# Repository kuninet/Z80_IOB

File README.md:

View this project on [CADLAB.io](https://cadlab.io/project/23712). 

# Z80 I/Oボード (KZ80-IOB)

詳細は[以下のwiki](https://github.com/kuninet/Z80_IOB/wiki)にまとめます。
ご覧ください。

https://github.com/kuninet/Z80_IOB/wiki

## 概要

- SBC8080ルーズキットバスにつながるI/Oボードです。
  - [Z80 CPUボード(KZ80-CPUB)](https://github.com/kuninet/Z80_CPUB/wiki)、[SBC8080](https://vintagechips.wordpress.com/2018/06/24/sbc8080-cpu%E3%83%AB%E3%83%BC%E3%82%BA%E3%82%AD%E3%83%83%E3%83%88/)、[SBC8085](https://vintagechips.wordpress.com/2018/08/27/sbc8085%e3%81%8c%e5%ae%8c%e6%88%90/)と組み合わせた稼働を確認しています。
  - 8255パラレルI/O LSIを搭載しています。(Lチカに最適)
  - 8251シリアルチップを搭載しています。
  - 将来 ArduinoコネクタのFM音源シールドを搭載するためのコネクタを装備しています。(これ以外の使いみちはありませんが...)

## 回路図

[回路図はこちら](image/Z80-8251-PPI.pdf)です。

## 部品表

[部品表はこちら](KiCAD/Z80-8251-PPI.ods)です。

※LibreOffice/OpenOfficeのcalcで開ける形式となっています。

## ライセンス

- 本リポジトリのデータは MIT License のもとで公開します。[LICENSE.txt](LICENSE.txt)を参照して下さい。

## その他注意点等

- 8251シリアルLSIのアドレスデコードをSBC8080 SUBボードと合わせる場合は、アドレスデコードジャンパ(J2)の1-2を短絡(I/Oアドレス:00h)してください。
- 8255パラレルI/O LSIのアドレスデコードジャンパ(J3)は 13-14を短絡(I/Oアドレス:C0h)が推奨です。

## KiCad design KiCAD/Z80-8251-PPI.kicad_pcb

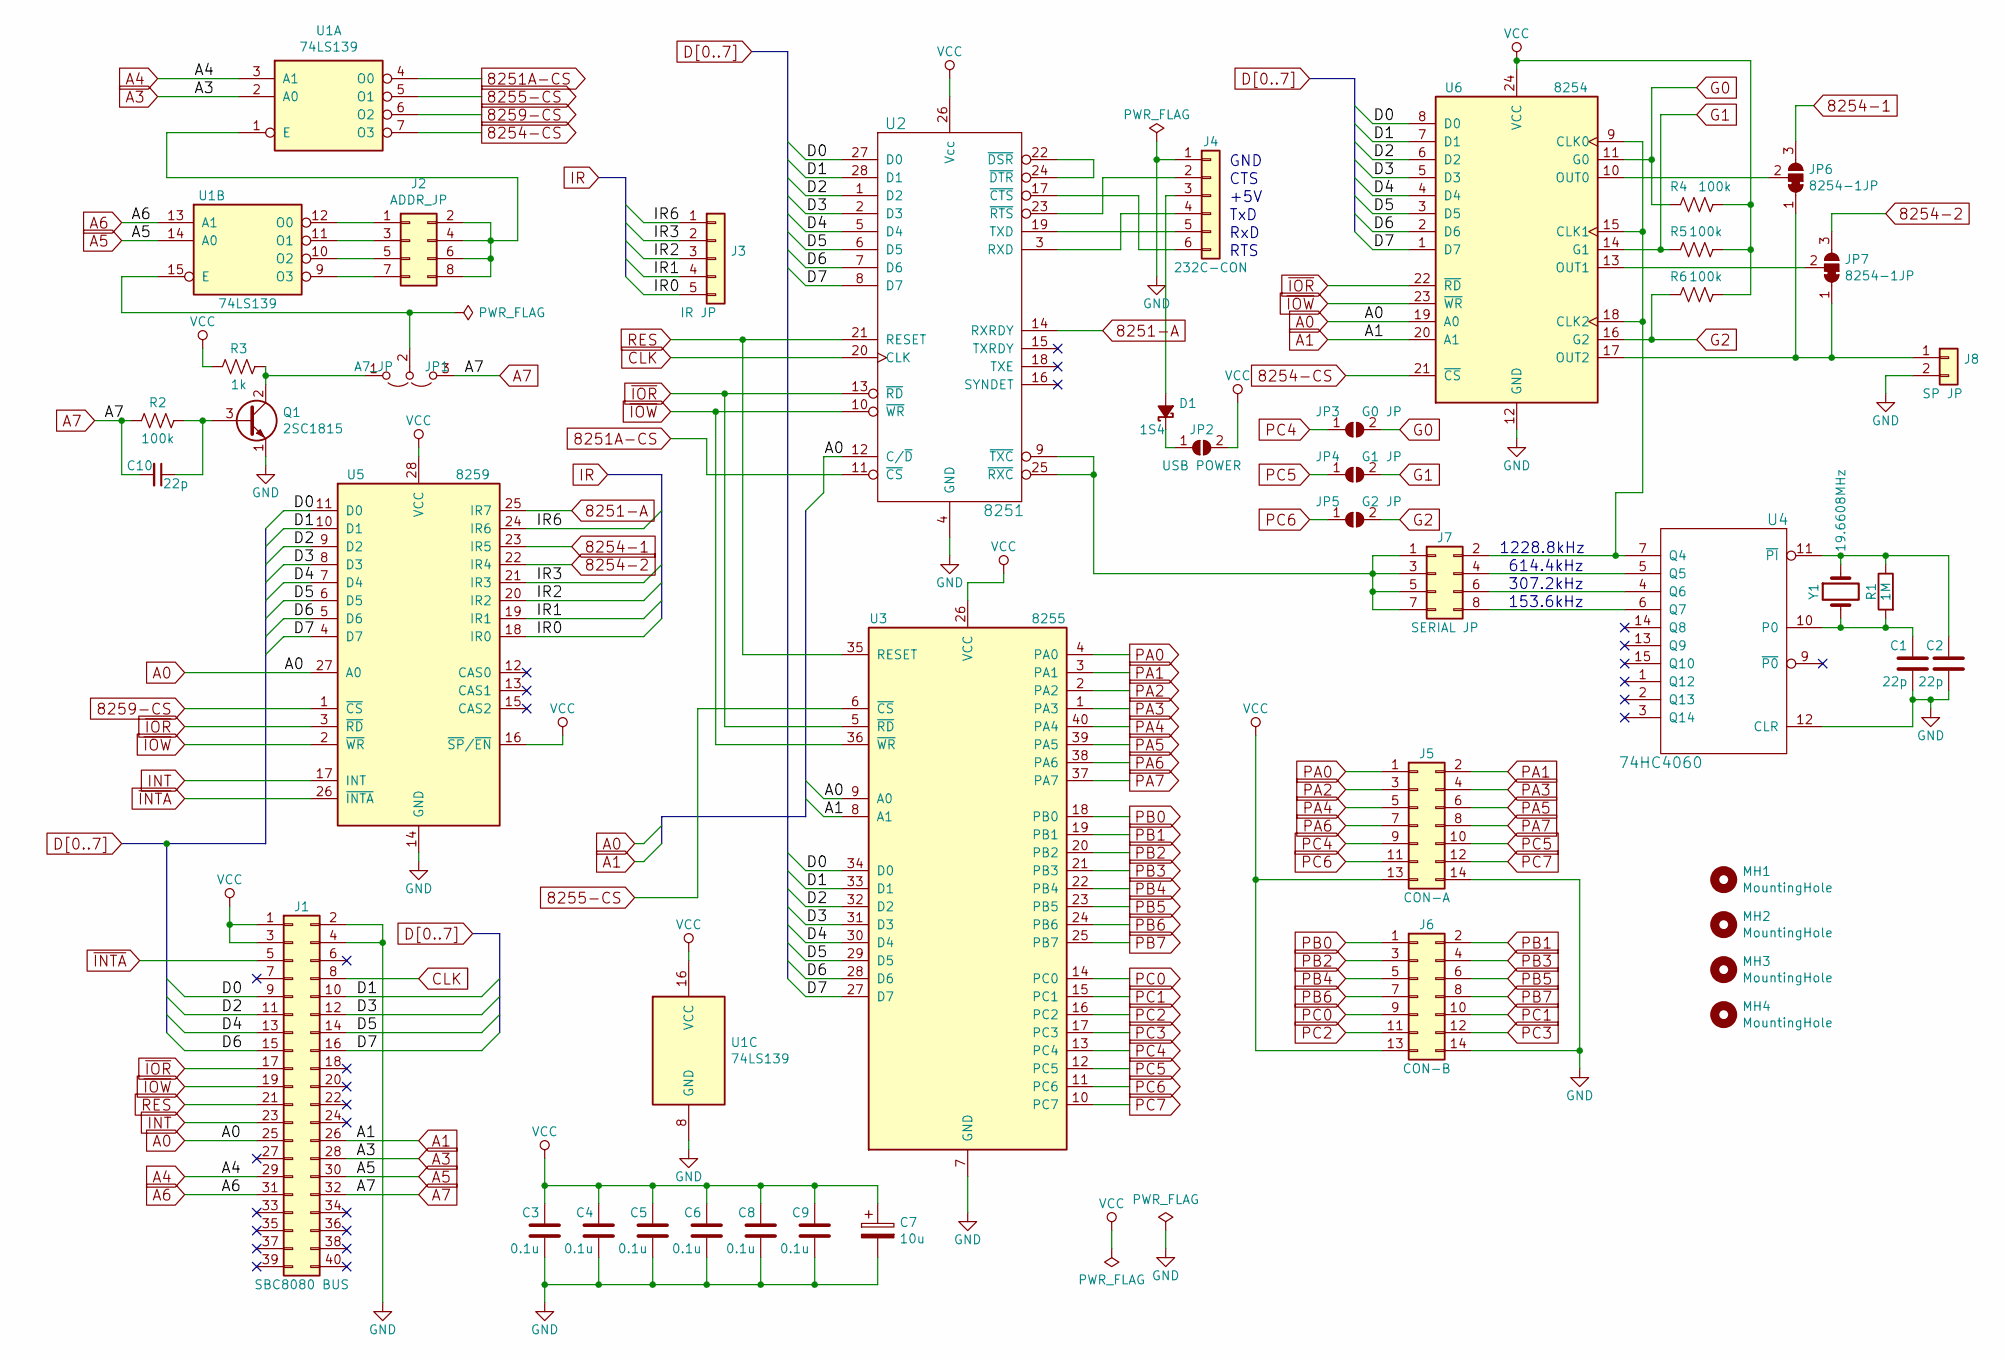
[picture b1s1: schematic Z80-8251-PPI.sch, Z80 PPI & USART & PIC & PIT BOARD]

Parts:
C1, C2, C10: 22p; C_Disc_D3.0mm_W1.6mm_P2.50mm
C3, C4, C5, C6, C8, C9: 0.1u; C_Disc_D3.0mm_W1.6mm_P2.50mm
C7: 10u; CP_Radial_D5.0mm_P2.50mm
D1: 1S4; D_DO-34_SOD68_P7.62mm_Horizontal
J1: SBC8080 BUS; Pin_Header_Angled_2x20
J2: ADDR_JP; PinHeader_2x04_P2.54mm_Vertical
J3: IR JP; PinHeader_1x05_P2.54mm_Horizontal
J4: 232C-CON; PinHeader_1x06_P2.54mm_Horizontal
J5: CON-A; PinHeader_2x07_P2.54mm_Vertical
J6: CON-B; PinHeader_2x07_P2.54mm_Vertical
J7: SERIAL JP; PinHeader_2x04_P2.54mm_Vertical
J8: SP JP; PinHeader_1x02_P2.54mm_Horizontal
JP1: A7_JP; PinHeader_1x03_P2.54mm_Vertical
JP2: USB POWER; SolderJumper-2_P1.3mm_Open_RoundedPad1.0x1.5mm
JP3: G0 JP; SolderJumper-2_P1.3mm_Open_RoundedPad1.0x1.5mm
JP4: G1 JP; SolderJumper-2_P1.3mm_Open_RoundedPad1.0x1.5mm
JP5: G2 JP; SolderJumper-2_P1.3mm_Open_RoundedPad1.0x1.5mm
JP6, JP7: 8254-1JP; SolderJumper-3_P1.3mm_Bridged12_RoundedPad1.0x1.5mm
MH1, MH2, MH3, MH4: MountingHole; MountingHole_3.2mm_M3
Q1: 2SC1815; TO-92_Inline_Wide
R1: 1M; R_Axial_DIN0207_L6.3mm_D2.5mm_P10.16mm_Horizontal
R2, R4, R5, R6: 100k; R_Axial_DIN0207_L6.3mm_D2.5mm_P10.16mm_Horizontal
R3: 1k; R_Axial_DIN0207_L6.3mm_D2.5mm_P10.16mm_Horizontal
U1: 74LS139; DIP-16_W7.62mm_Socket
U2: 8251; DIP-28_W15.24mm_Socket
U3: 8255; DIP-40_W15.24mm_Socket
U4: 74HC4060; DIP-16_W7.62mm_Socket
U5: 8259; DIP-28_W15.24mm_Socket
U6: 8254; DIP-24_W15.24mm_Socket
Y1: 19.6608MHz; HC-49V

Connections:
8251-A: U2.14 (RXRDY), U5.25 (IR7)
8251A-CS: U1.4 (O0), U2.11 (~CS)
8254-1: JP6.3 (B), U5.23 (IR5)
8254-2: JP7.3 (B), U5.22 (IR4)
8254-CS: U1.7 (O3), U6.21 (~CS~)
8255-CS: U1.5 (O1), U3.6 (~CS~)
8259-CS: U1.6 (O2), U5.1 (~CS~)
/IR0: J3.5, U5.18 (IR0)
/IR1: J3.4, U5.19 (IR1)
/IR2: J3.3, U5.20 (IR2)
/IR3: J3.2, U5.21 (IR3)
/IR6: J3.1, U5.24 (IR6)
A0: J1.25, U2.12 (C/~D), U3.9 (A0), U5.27 (A0), U6.19 (A0)
A1: J1.26, U3.8 (A1), U6.20 (A1)
A3: J1.28, U1.2 (A0)
A4: J1.29, U1.3 (A1)
A5: J1.30, U1.14 (A0)
A6: J1.31, U1.13 (A1)
A7: C10.2, J1.32, JP1.3 (B), R2.2
CLK: J1.8, U2.20 (CLK)
D0: J1.9, U2.27 (D0), U3.34 (D0), U5.11 (D0), U6.8 (D0)
D1: J1.10, U2.28 (D1), U3.33 (D1), U5.10 (D1), U6.7 (D1)
D2: J1.11, U2.1 (D2), U3.32 (D2), U5.9 (D2), U6.6 (D2)
D3: J1.12, U2.2 (D3), U3.31 (D3), U5.8 (D3), U6.5 (D3)
D4: J1.13, U2.5 (D4), U3.30 (D4), U5.7 (D4), U6.4 (D4)
D5: J1.14, U2.6 (D5), U3.29 (D5), U5.6 (D5), U6.3 (D5)
D6: J1.15, U2.7 (D6), U3.28 (D6), U5.5 (D6), U6.2 (D6)
D7: J1.16, U2.8 (D7), U3.27 (D7), U5.4 (D7), U6.1 (D7)
G0: JP3.2 (B), R4.2, U6.11 (G0)
G1: JP4.2 (B), R5.2, U6.14 (G1)
G2: JP5.2 (B), R6.2, U6.16 (G2)
GND: C1.2, C2.2, C3.2, C4.2, C5.2, C6.2, C7.2, C8.2, C9.2, J1.2, J1.4, J4.1, J5.14, J6.14, J8.2, Q1.1 (E), U1.8 (GND), U2.4 (GND), U3.7 (GND), U4.8 (GND), U4.12 (CLR), U5.14 (GND), U6.12 (GND)
INT: J1.23, U5.17 (INT)
unnamed: C1.1, R1.2, U4.10 (P0), Y1.2
unnamed: C2.1, R1.1, U4.11 (~PI), Y1.1
unnamed: C10.1, Q1.3 (B), R2.1
unnamed: D1.1 (K), JP2.1 (A)
unnamed: D1.2 (A), J4.3
unnamed: J2.1, U1.12 (O0)
unnamed: J2.2, J2.4, J2.6, J2.8, U1.1 (E)
unnamed: J2.3, U1.11 (O1)
unnamed: J2.5, U1.10 (O2)
unnamed: J2.7, U1.9 (O3)
unnamed: J4.2, U2.23 (~RTS)
unnamed: J4.4, U2.3 (RXD)
unnamed: J4.5, U2.19 (TXD)
unnamed: J4.6, U2.17 (~CTS)
unnamed: J7.1, J7.3, J7.5, J7.7, U2.9 (~TXC), U2.25 (~RXC)
unnamed: J7.2, U4.7 (Q4), U6.9 (CLK0), U6.15 (CLK1), U6.18 (CLK2)
unnamed: J7.4, U4.5 (Q5)
unnamed: J7.6, U4.4 (Q6)
unnamed: J7.8, U4.6 (Q7)
unnamed: J8.1, JP6.1 (A), JP7.1 (A), U6.17 (OUT2)
unnamed: JP1.1 (A), Q1.2 (C), R3.1
unnamed: JP1.2 (C), U1.15 (E)
unnamed: JP6.2 (C), U6.10 (OUT0)
unnamed: JP7.2 (C), U6.13 (OUT1)
unnamed: U2.22 (~DSR), U2.24 (~DTR)
PA0: J5.1, U3.4 (PA0)
PA1: J5.2, U3.3 (PA1)
PA2: J5.3, U3.2 (PA2)
PA3: J5.4, U3.1 (PA3)
PA4: J5.5, U3.40 (PA4)
PA5: J5.6, U3.39 (PA5)
PA6: J5.7, U3.38 (PA6)
PA7: J5.8, U3.37 (PA7)
PB0: J6.1, U3.18 (PB0)
PB1: J6.2, U3.19 (PB1)
PB2: J6.3, U3.20 (PB2)
PB3: J6.4, U3.21 (PB3)
PB4: J6.5, U3.22 (PB4)
PB5: J6.6, U3.23 (PB5)
PB6: J6.7, U3.24 (PB6)
PB7: J6.8, U3.25 (PB7)
PC0: J6.9, U3.14 (PC0)
PC1: J6.10, U3.15 (PC1)
PC2: J6.11, U3.16 (PC2)
PC3: J6.12, U3.17 (PC3)
PC4: J5.9, JP3.1 (A), U3.13 (PC4)
PC5: J5.10, JP4.1 (A), U3.12 (PC5)
PC6: J5.11, JP5.1 (A), U3.11 (PC6)
PC7: J5.12, U3.10 (PC7)
RES: J1.21, U2.21 (RESET), U3.35 (RESET)
VCC: C3.1, C4.1, C5.1, C6.1, C7.1, C8.1, C9.1, J1.1, J1.3, J5.13, J6.13, JP2.2 (B), R3.2, R4.1, R5.1, R6.1, U1.16 (VCC), U2.26 (Vcc), U3.26 (VCC), U4.16 (VCC), U5.16 (~SP~/~EN~), U5.28 (VCC), U6.24 (VCC)
~INTA: J1.5, U5.26 (~INTA~)
~IOR: J1.17, U2.13 (~RD), U3.5 (~RD~), U5.3 (~RD~), U6.22 (~RD~)
~IOW: J1.19, U2.10 (~WR), U3.36 (~WR~), U5.2 (~WR~), U6.23 (~WR~)

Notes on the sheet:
1228.8kHz
614.4kHz
307.2kHz
153.6kHz
GND
CTS
+5V
TxD
RxD
RTS

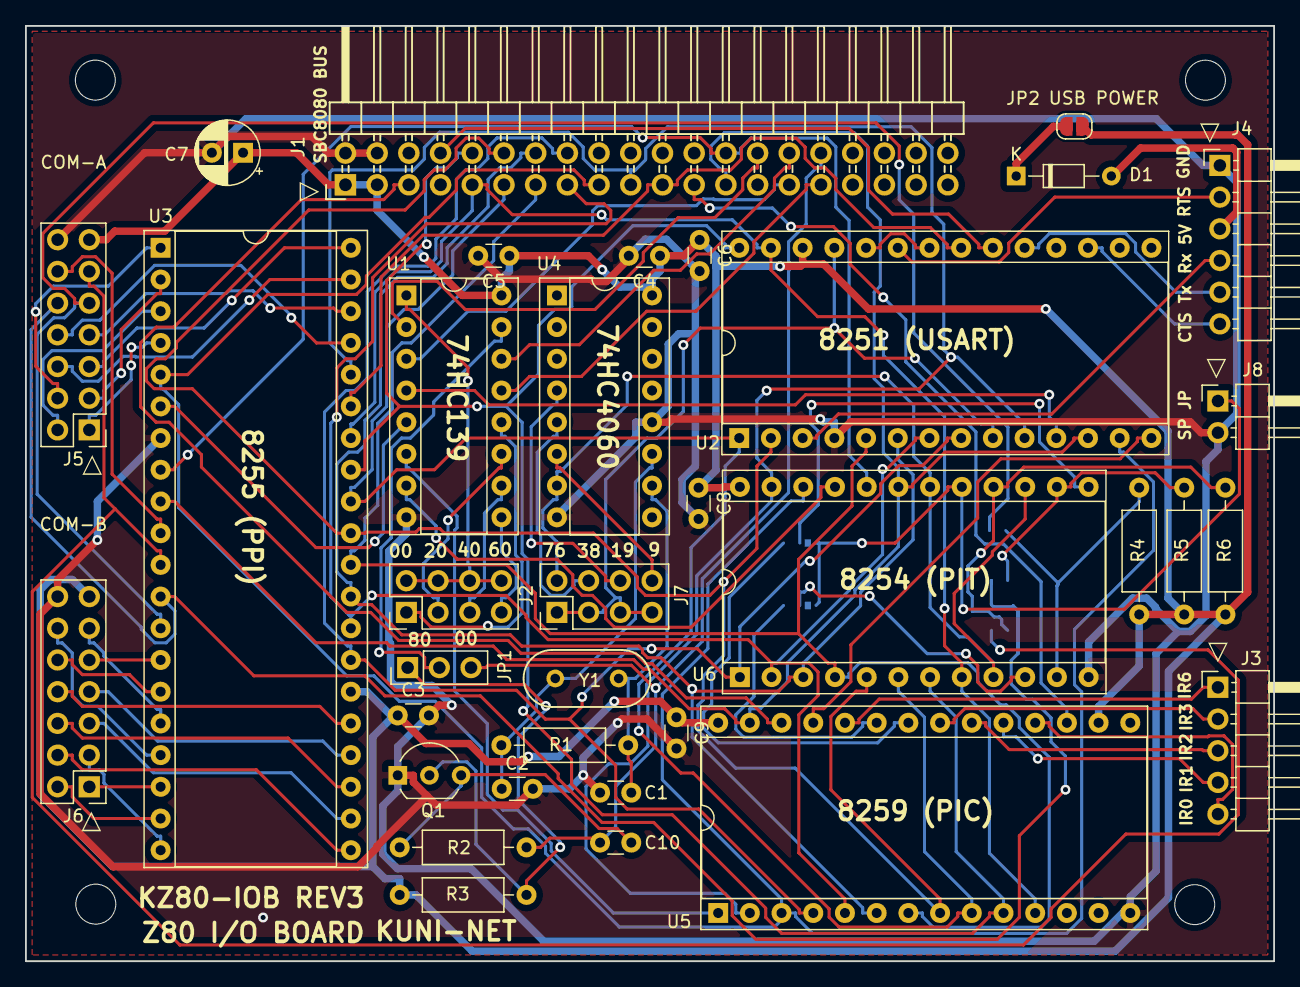
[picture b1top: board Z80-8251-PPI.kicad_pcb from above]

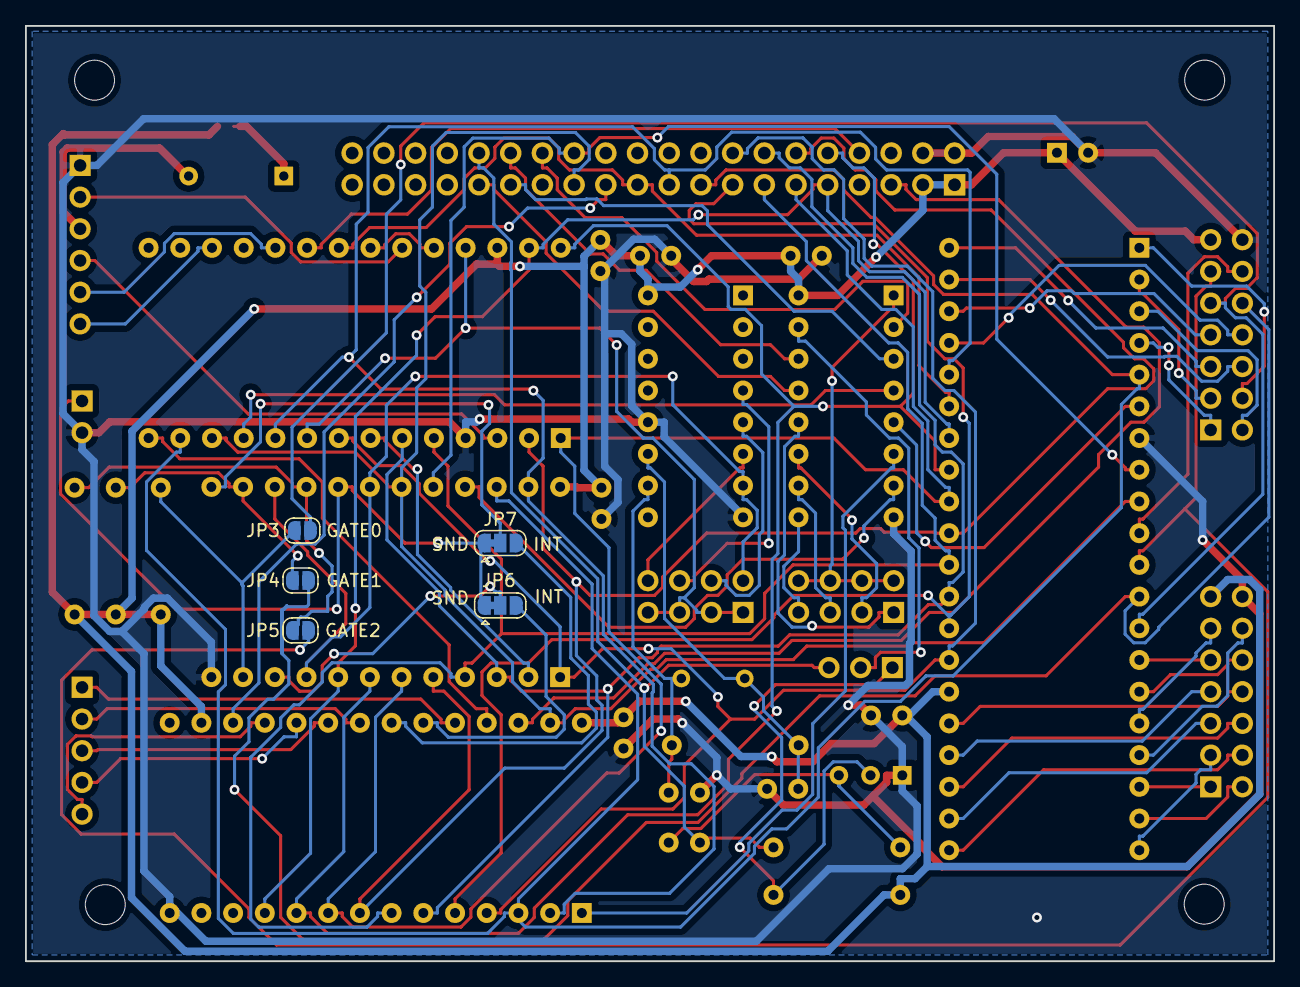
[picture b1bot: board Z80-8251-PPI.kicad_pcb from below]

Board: 2 copper layers, 100.0 x 74.9 mm, 44 parts (5 on the bottom side), 87 nets.

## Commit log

2018-09-30 init commit
2018-10-07 KiCADデータ等整備
2018-10-22 PPIコネクタ再配置、電解コンデンサ追加、シルク見直し
2018-11-18 Rev1.1パターン見直し
2018-11-18 REV1.1回路図更新
2018-11-18 部品表修正
2019-03-17 REV2 回路図、製造データ出力
2019-03-17 旧回路図(REV1) 別ファイルへ
2019-03-30 ロジックICで割り込みコントローラ構成を検討 ドラフト版
2020-08-08 REV3 回路図、パターン検討 その1
2020-08-08 FTDI +5Vへダイオード追加
2021-01-06 Backlink to CADLAB.io has been added.
2022-05-04 LED ブリンクサンプル追加
